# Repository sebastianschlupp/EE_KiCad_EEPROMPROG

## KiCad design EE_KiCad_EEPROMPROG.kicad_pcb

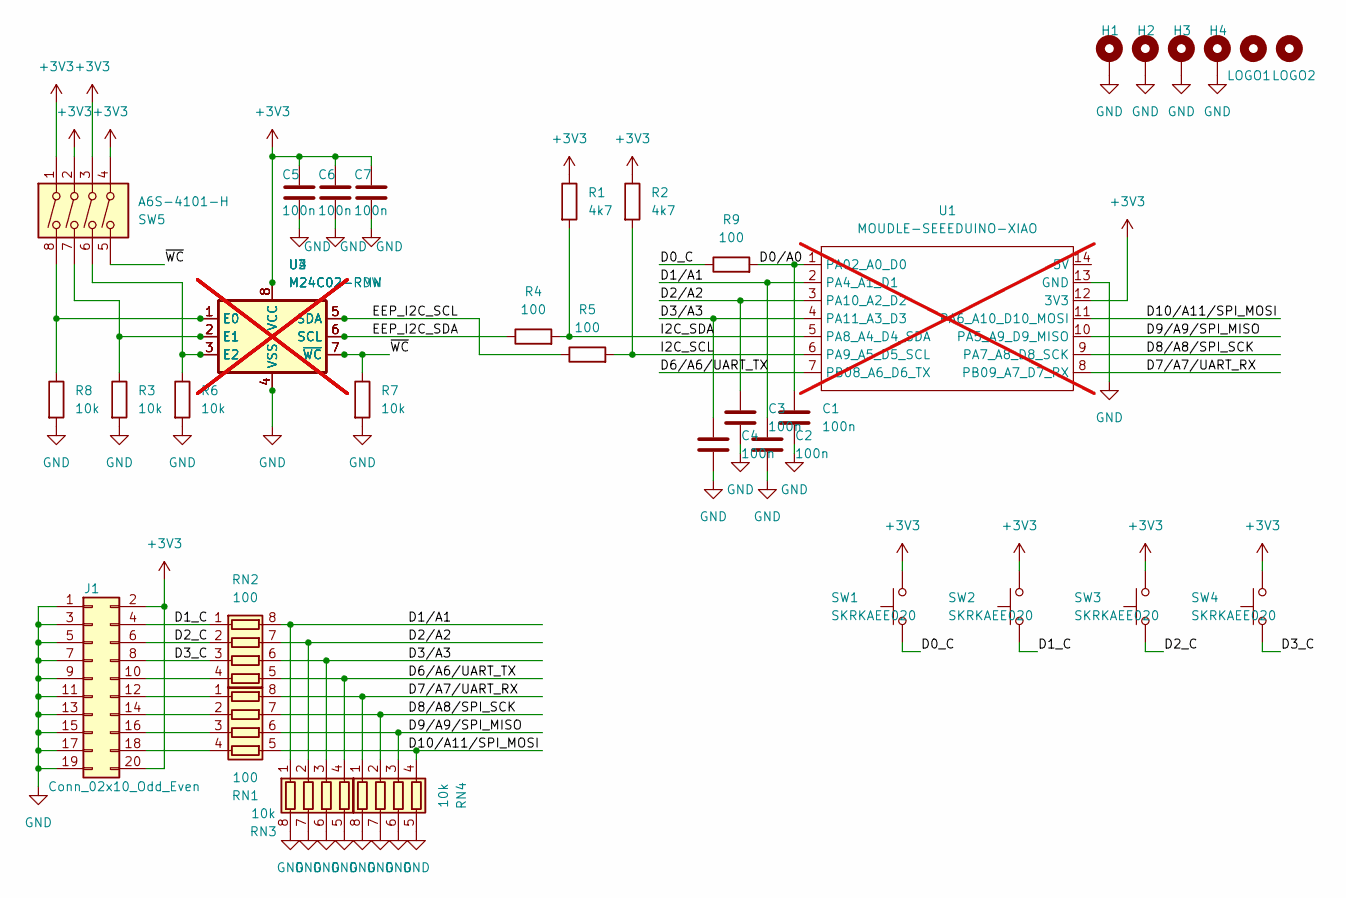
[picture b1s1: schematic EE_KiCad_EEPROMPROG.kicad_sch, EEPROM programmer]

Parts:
C1, C2, C3, C4, C5, C6, C7: 100n; C_0402_1005Metric; MPN CC0402KRX7R7BB104
H1, H2, H3, H4: MountingHole_Pad; MountingHole_2.7mm_M2.5_ISO7380_Pad_TopBottom
J1: Conn_02x10_Odd_Even; PinHeader_2x10_P2.54mm_Vertical_SMD; MPN TSM-110-01-L-DV-P-TR
LOGO1, LOGO2: MountingHole; TardigradeLogo_v3
R1, R2: 4k7; R_0402_1005Metric; MPN AF0402JR-074K7RL
R3, R6, R7, R8: 10k; R_0402_1005Metric; MPN AF0402JR-0710KRL
R4, R5, R9: 100; R_0402_1005Metric; MPN AF0402JR-07100RL
RN1, RN2: 100; R_Array_Concave_4x0603; MPN YC164-JR-07100RL
RN3, RN4: 10k; R_Array_Concave_4x0603; MPN YC164-JR-0710KRL
SW1, SW2, SW3, SW4: SKRKAEE020; SW_Push_SPST_NO_Alps_SKRK; MPN SKRKAEE020
SW5: A6S-4101-H; SW_DIP_SPSTx04_Slide_Omron_A6S-410x_W8.9mm_P2.54mm; MPN A6S-4101-H
U1: MOUDLE-SEEEDUINO-XIAO; MOUDLE14P-2.54-21X17.8MM_SMTTHTcombo; not fitted
U2: M24C02-RDW; TSSOP-8_4.4x3mm_P0.65mm; not fitted
U3: M24C02-RMN; SOIC-8_3.9x4.9mm_P1.27mm; not fitted
U4: M24C02; DIP-8_W7.62mm_Socket; not fitted

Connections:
+3V3: C5.1, C6.1, C7.1, J1.2, J1.20, R1.1, R2.1, SW1.2, SW2.2, SW3.2, SW4.2, SW5.1, SW5.2, SW5.3, SW5.4, U1.12 (3V3), U2.8 (VCC), U3.8 (VCC), U4.8 (VCC)
/D0_C: R9.1, SW1.1
/D0/A0: C1.1, R9.2, U1.1 (PA02_A0_D0)
/D1_C: J1.4, RN2.1 (R1.1), SW2.1
/D1/A1: C2.1, RN2.8 (R1.2), RN3.1 (R1.1), U1.2 (PA4_A1_D1)
/D2_C: J1.6, RN2.2 (R2.1), SW3.1
/D2/A2: C3.1, RN2.7 (R2.2), RN3.2 (R2.1), U1.3 (PA10_A2_D2)
/D3_C: J1.8, RN2.3 (R3.1), SW4.1
/D3/A3: C4.1, RN2.6 (R3.2), RN3.3 (R3.1), U1.4 (PA11_A3_D3)
/D6/A6/UART_TX: RN2.5 (R4.2), RN3.4 (R4.1), U1.7 (PB08_A6_D6_TX)
/D7/A7/UART_RX: RN1.8 (R1.2), RN4.1 (R1.1), U1.8 (PB09_A7_D7_RX)
/D8/A8/SPI_SCK: RN1.7 (R2.2), RN4.2 (R2.1), U1.9 (PA7_A8_D8_SCK)
/D9/A9/SPI_MISO: RN1.6 (R3.2), RN4.3 (R3.1), U1.10 (PA5_A9_D9_MISO)
/D10/A11/SPI_MOSI: RN1.5 (R4.2), RN4.4 (R4.1), U1.11 (PA6_A10_D10_MOSI)
/EEP_I2C_SCL: R5.1, U2.5 (SDA), U3.5 (SDA), U4.5 (SDA)
/EEP_I2C_SDA: R4.1, U2.6 (SCL), U3.6 (SCL), U4.6 (SCL)
/I2C_SCL: R2.2, R5.2, U1.6 (PA9_A5_D5_SCL)
/I2C_SDA: R1.2, R4.2, U1.5 (PA8_A4_D4_SDA)
/~WC: R7.1, SW5.5, U2.7 (~WC), U3.7 (~WC), U4.7 (~WC)
GND: C1.2, C2.2, C3.2, C4.2, C5.2, C6.2, C7.2, H1.1, H2.1, H3.1, H4.1, J1.1, J1.3, J1.5, J1.7, J1.9, J1.11, J1.13, J1.15, J1.17, J1.19, R3.2, R6.2, R7.2, R8.2, RN3.5 (R4.2), RN3.6 (R3.2), RN3.7 (R2.2), RN3.8 (R1.2), RN4.5 (R4.2), RN4.6 (R3.2), RN4.7 (R2.2), RN4.8 (R1.2), U1.13 (GND), U2.4 (VSS), U3.4 (VSS), U4.4 (VSS)
unnamed: J1.10, RN2.4 (R4.1)
unnamed: J1.12, RN1.1 (R1.1)
unnamed: J1.14, RN1.2 (R2.1)
unnamed: J1.16, RN1.3 (R3.1)
unnamed: J1.18, RN1.4 (R4.1)
unnamed: R8.1, SW5.8, U2.1 (E0), U3.1 (E0), U4.1 (E0)
unnamed: R3.1, SW5.7, U2.2 (E1), U3.2 (E1), U4.2 (E1)
unnamed: R6.1, SW5.6, U2.3 (E2), U3.3 (E2), U4.3 (E2)

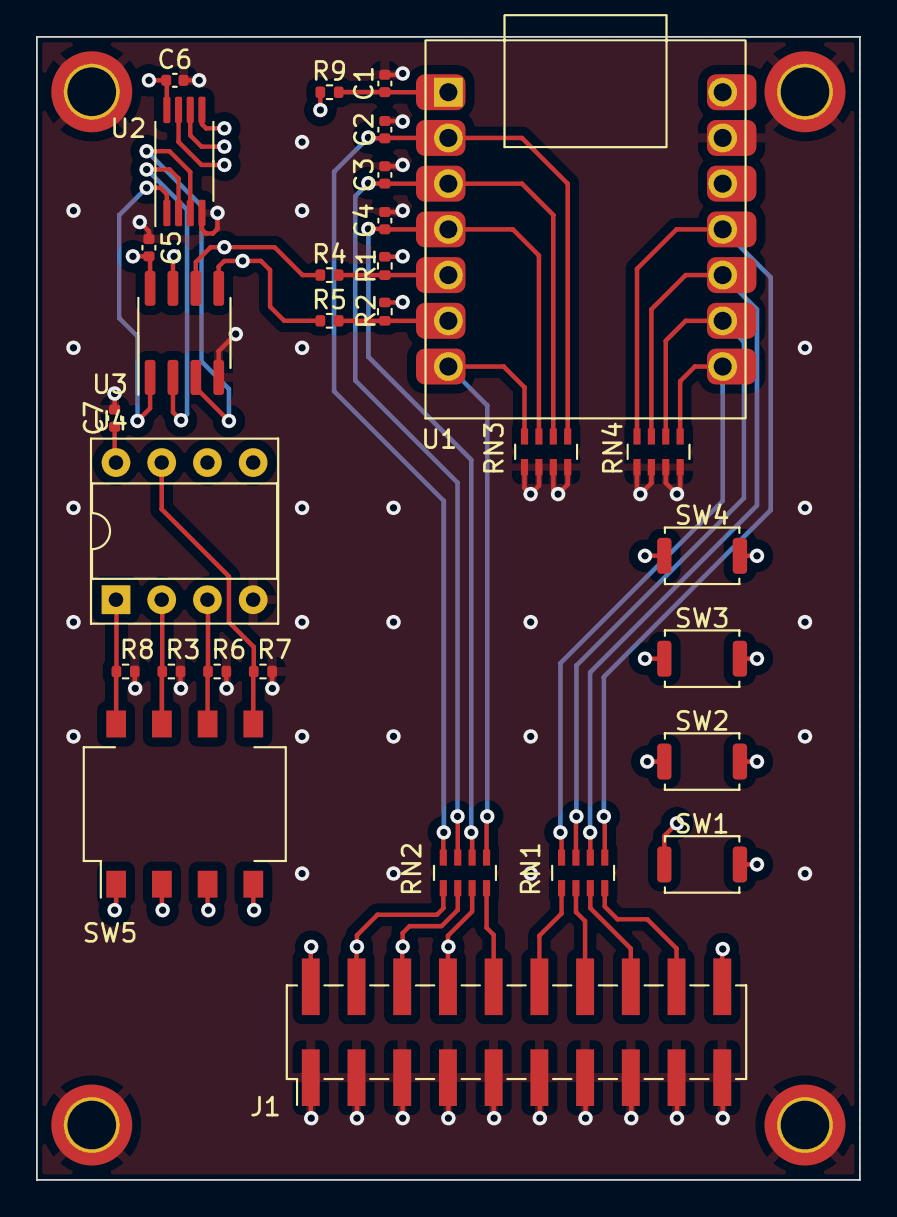
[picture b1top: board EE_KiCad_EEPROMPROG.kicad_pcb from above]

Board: 6 copper layers, 45.7 x 63.5 mm, 36 parts (1 on the bottom side), 28 nets.

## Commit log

2024-02-23 Initial release EEPROM programming board based on the Seeed Studio Xiao RP2040
2024-02-23 Initial Release Initial Release
